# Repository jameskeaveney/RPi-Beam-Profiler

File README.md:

Raspberry Pi Beam Profiler
==========================
**Version 1.0.0**

A platform for inexpensive automatic laser beam profiling for finding the focal position and beam width of a laser beam, using a commercial translation stage, stepper motor, raspberry pi computer and the Pi NoIR camera module.

This repository contains the electronics schematics, mechanical drawings, list of components and python codes to construct and run the Raspberry Pi Beam Profiler.

See the user guide PDF for detailed installation instructions.

The paper, currently available on the arxiv (arxiv.org/abs/...), details the operation and exemplifies some results from the beam profiler.

-----------------

**Revision History**

v1.0.0
- Initial commit

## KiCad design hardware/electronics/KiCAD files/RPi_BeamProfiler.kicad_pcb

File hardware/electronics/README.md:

These are the electronic design files for the RPi beam profiler. 

The design files use KiCAD (http://kicad-pcb.org/). The PCB designs can be uploaded in their current .kicad_pcb file format to oshpark.com for board manufacture. If gerber files are required, open the pcb file in KiCAD first and output gerber files from there.

The daughter board sits on top of the RPi GPIO pins, and includes:

> A high-current 5V voltage regulator to power the RPi
> The Pololu DRV8825 motor controller breakout board

This should be powered by a high current (> 2A) DC voltage supplied via the barrel connector (centre positive).

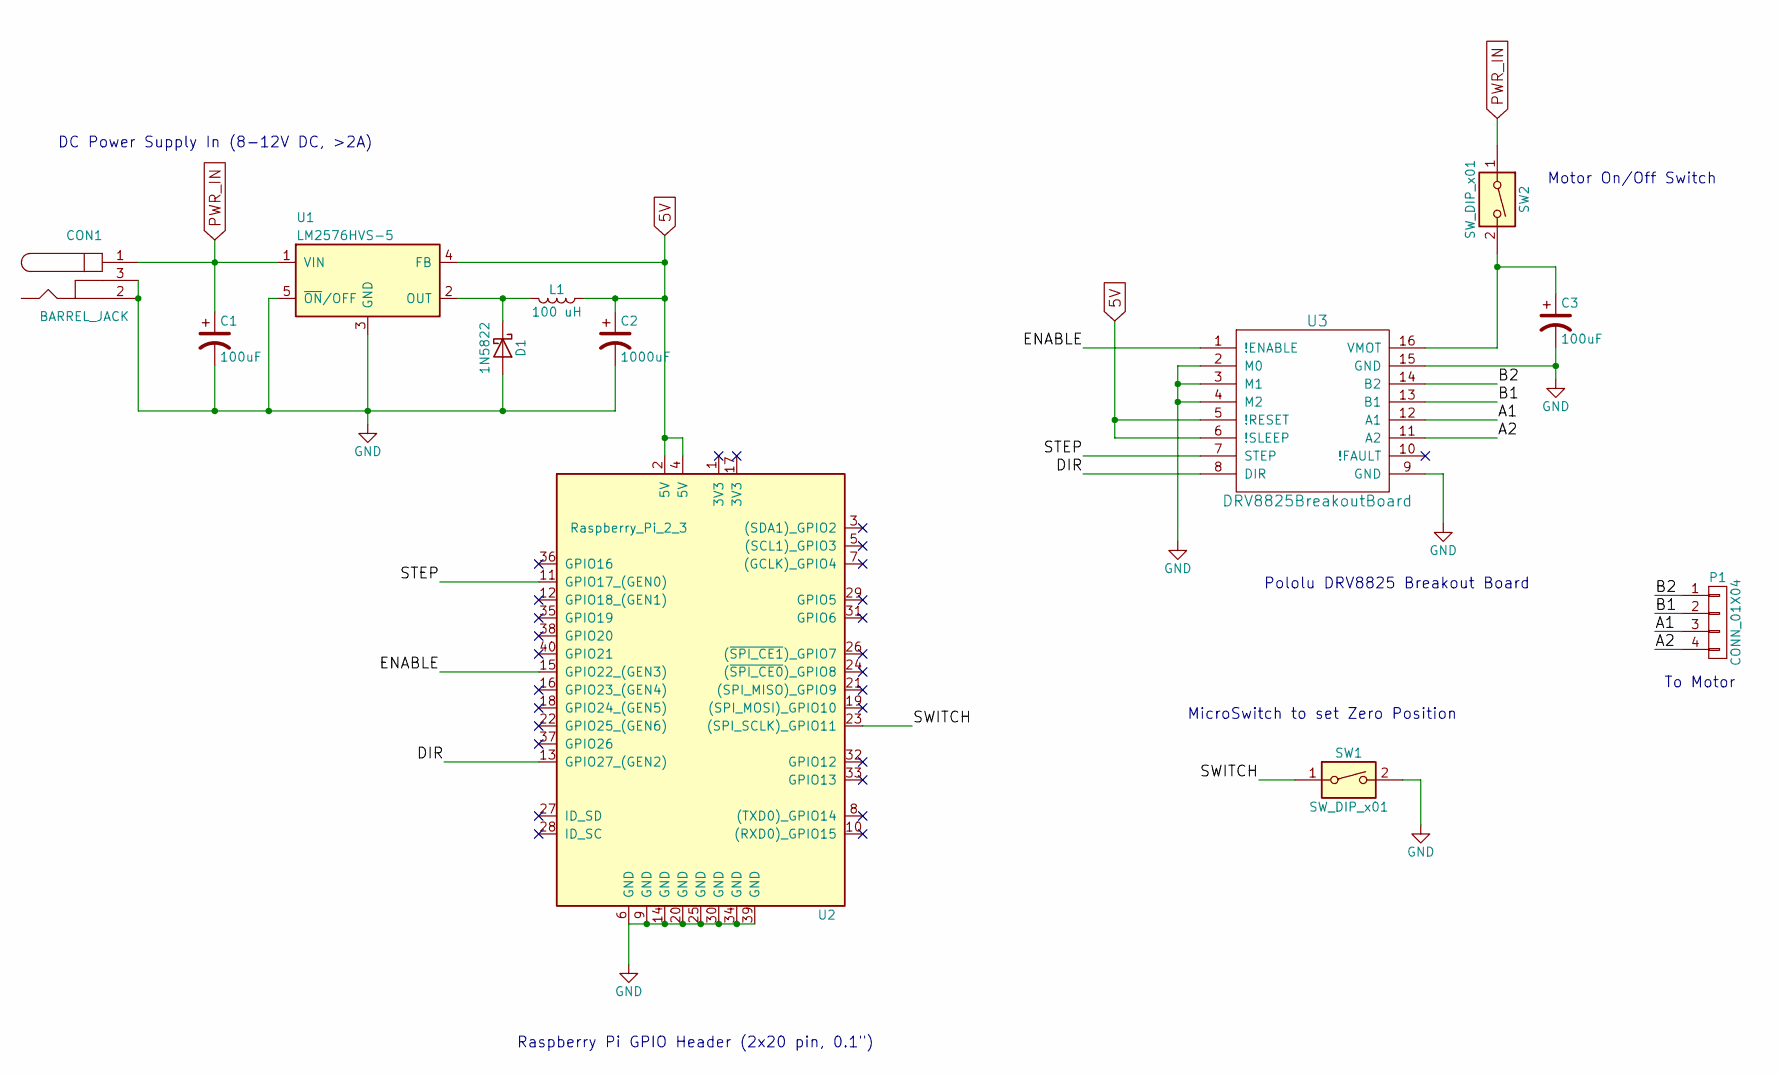
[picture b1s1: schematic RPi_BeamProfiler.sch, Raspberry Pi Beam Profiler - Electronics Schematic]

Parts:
C1, C3: 100uF; CP_Radial_D6.3mm_P2.50mm
C2: 1000uF; CP_Radial_D10.0mm_P5.00mm
CON1: BARREL_JACK
D1: 1N5822; D_5W_P5.08mm_Vertical_AnodeUp
L1: 100 uH; INDUCTOR_V
P1: CONN_01X04; Pin_Header_Straight_1x04_Pitch2.54mm
SW1: SW_DIP_x01; Pin_Header_Straight_1x02_Pitch2.54mm
SW2: SW_DIP_x01; SW_DIP_x1_W7.62mm_Slide_LowProfile
U1: LM2576HVS-5; TO-220-5_Pentawatt_Multiwatt-5_Vertical_StaggeredType1
U2: Raspberry_Pi_2_3; Pin_Header_Straight_2x20_Pitch2.54mm
U3: DRV8825BreakoutBoard; DRV8825_BreakoutBoard

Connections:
5V: C2.1, L1.1, U1.4 (FB), U2.2 (5V), U2.4 (5V), U3.5 (!RESET), U3.6 (!SLEEP)
/A1: P1.3, U3.12 (A1)
/A2: P1.4, U3.11 (A2)
/B1: P1.2, U3.13 (B1)
/B2: P1.1, U3.14 (B2)
/DIR: U2.13 (GPIO27_(GEN2)), U3.8 (DIR)
/ENABLE: U2.15 (GPIO22_(GEN3)), U3.1 (!ENABLE)
/STEP: U2.11 (GPIO17_(GEN0)), U3.7 (STEP)
/SWITCH: SW1.1, U2.23 ((SPI_SCLK)_GPIO11)
GND: C1.2, C2.2, C3.2, CON1.2, CON1.3, D1.2 (A), SW1.2, U1.3 (GND), U1.5 (~ON~/OFF), U2.6 (GND), U2.9 (GND), U2.14 (GND), U2.20 (GND), U2.25 (GND), U2.30 (GND), U2.34 (GND), U2.39 (GND), U3.2 (M0), U3.3 (M1), U3.4 (M2), U3.9 (GND), U3.15 (GND)
unnamed: C3.1, SW2.2, U3.16 (VMOT)
unnamed: D1.1 (K), L1.2, U1.2 (OUT)
PWR_IN: C1.1, CON1.1, SW2.1, U1.1 (VIN)

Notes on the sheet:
DC Power Supply In (8-12V DC, >2A)
Raspberry Pi GPIO Header (2x20 pin, 0.1")
Pololu DRV8825 Breakout Board
MicroSwitch to set Zero Position
Motor On/Off Switch
To Motor

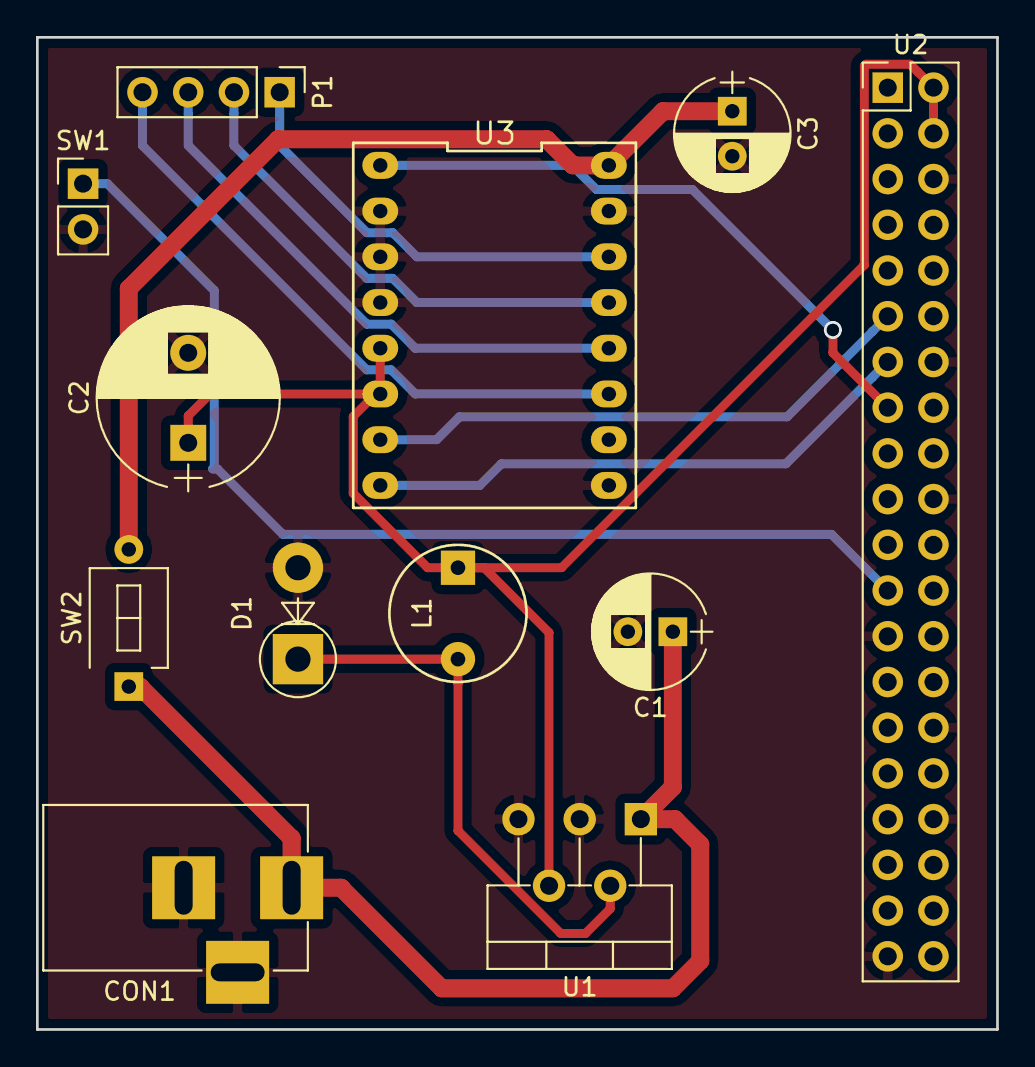
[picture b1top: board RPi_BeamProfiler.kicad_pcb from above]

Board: 2 copper layers, 53.3 x 55.1 mm, 12 parts (0 on the bottom side), 13 nets.

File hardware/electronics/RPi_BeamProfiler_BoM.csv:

Id,Designator,Package,Quantity,Designation,Supplier and ref
1,"C1,C3",CP_Radial_D6.3mm_P2.50mm,2,100uF,
2,C2,CP_Radial_D10.0mm_P5.00mm,1,1000uF,
3,CON1,BARREL_JACK,1,BARREL_JACK,
4,D1,D_5W_P5.08mm_Vertical_AnodeUp,1,1N5822,
5,L1,INDUCTOR_V,1,100 uH,
6,SW1,Pin_Header_Straight_1x02_Pitch2.54mm,1,SW_DIP_x01,
7,SW2,SW_DIP_x1_W7.62mm_Slide_LowProfile,1,SW_DIP_x01,
8,U1,TO-220-5_Pentawatt_Multiwatt-5_Vertical_StaggeredType1,1,LM2576HVS-5,
9,U3,DRV8825_BreakoutBoard,1,DRV8825BreakoutBoard,
10,U2,Pin_Header_Straight_2x20_Pitch2.54mm,1,Raspberry_Pi_2_3,
11,P1,Pin_Header_Straight_1x04_Pitch2.54mm,1,CONN_01X04,
,,,,,
"Plus additional 0.1"" headers for attaching connecting the DRV8825 breakout board (e.g. http://www.hobbytronics.co.uk/cables-connectors/pcb-headers-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",,,,,

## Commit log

2018-01-19 Initial Commit
    Initial commit of version 1 files.
2018-01-19 Initial Commit
    Initial commit
2018-01-19 Initial Commit
    Initial commit (file replacement)
2019-08-28 Add files via upload
    numpy no longer accepts floats for indexes. cast roi as ints
2024-01-18 Convert to python3, black and isort, some minor fixes
2024-01-18 gitignore
2024-01-18 Add vscode settings
